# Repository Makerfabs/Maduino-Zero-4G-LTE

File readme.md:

# Maduino Zero 4G LTE

```c++
/*
Version:		V1.1
Author:			Vincent
Create Date:	2021/11/5
Note:
	2022/12/30	V1.1:	Change Wiki link.
*/
```

[toc]

# Makerfabs

[Makerfabs home page](https://www.makerfabs.com/)

[Makerfabs Wiki](https://wiki.makerfabs.com/)

# Maduino Zero 4G LTE
## Intruduce

Product Link ：[Maduino Zero 4G LTE(SIM7600X)](https://www.makerfabs.com/maduino-zero-4g-lte-sim7600.html) 

Wiki Link : [Maduino Zero 4G LTE](http://wiki.makerfabs.com/Maduino_Zero_4G_LTE.html) 

Maduino Zero 4G LTE integrated two types of the 4G LTE CAT4 module SIM7600A-H or SIM7600E-H, SIM7600A-H/SIM7600E-H is a complete multi-band LTE-FDD/LTE-TDD/HSPA+/UMTS/EDGE/GPRS/GSM module solution in LCC type which supports LTE CAT4 up to 150Mbps for downlink and 50Mbps for uplink data transfer, much faster and popular than 2G/3G.

## Module Type

## Feature

- Supports dial-up, phone, SMS, TCP, UDP, DTMF, HTTP, FTP, and so on
- Dual USB Type C port
- Control Via AT Commands
- Board USB supply voltage range: 4.8~5.5V, 5.0V Typical
- Board Battery supply voltage range: 3.4~4.2V, 3.7V Typical
- 3GPP E-UTRA Release 11
- Onboard charger, up to 1A charge current
- Overcharge protection(OCP), 4.3V
- Over-discharge protection(ODP), 2.5V
- Power Manager, the board can be supplied by USB or battery.
- IPEX Antenna, GSM/UMTS/LTE main antenna. UMTS/LTE auxiliary antenna. GNSS antenna
- SMS support
- Audio support
- On boarder controller: ATSAMD21G18A
- Audio chip: NAU8810
- Level Shifter: TXS0108E

### Front:

### Back:

### Frequency bands

### Transfer Speed

# Usage （Arduino）

## Equipment list

- Maduino Zero 4G (With GPS antenna and two 4G-GSM antennas)
- SIM card 

*Ensure that SIM7600 requirements are met and that the system can communicate with local carriers. We used China Mobile's 4G card for testing.*

## Compiler Options

**If you have any questions，such as how to install the development board, how to download the code, how to install the library. Please refer to :[Makerfabs_FAQ](https://github.com/Makerfabs/Makerfabs_FAQ)**

- Connect all antennas
- Insert a SIM card
- Connect **USB for MCU** to PC

- Upload codes, select "Arduino Zero" and "Native USB"

## Example List

### AT_command_demo

Input AT commands via serial monitor to learn how to use 4G module. This version is modify for SIM7600.

If define MODE_1A, when "1A" or "1A" is entered, 0x1A is sent to the module.

When sending SNS information, you need to send 0x1A to end the input.

### 4G_HTTP_DHT11_V1.0

Air temperature and humidity information detected by the DHT11 module is sent to ThingSpeak using a cellular network.

## AT Command Explain

###  AT commands test

Refer to the official AT manual of SIM7600 for detailed return values.

```c++
    AT+CGMI    // Request manufacturer identification
    AT+CGMM    // Request model identification
    AT+CGSN    // Request product serial number identification
    AT+CSUB    // Request the module version and chip
    AT+CPIN?     // Request the state of the SIM card
    AT+CICCID    // Read ICCID from SIM card
    AT+CNUM      // Request the subscriber number
    AT+CNMP?     // Preferred mode selection
    AT+COPS?     // Check the current network operator
```

### Get the GNSS location

GPS signal acquisition speed depends on signal strength, please wait patiently in an open place.

```c++
    AT+CGPS=1      // Start GPS session 
    AT+CGPSINFO    // Get GPS fixed position information
    AT+CGPS=0      // Stop GPS session
```

### Send and receive SMS

Please consult the operator for the phone number of the SMS center. The number "+8613800755500" in Shenzhen was used in the test. 

```c++
    AT+CSCA="XXXXXX"       // Set the SMS service centre address
    AT+CMGF=1              // Select SMS message format
    AT+CMGS="xxxxxx"       // Send message to "xxxxxx"(the receiver number).
```

"AT+CMGS" sets the phone number of the receiver and returns ' >' . Send desired content, such as "Send Massage Test!".After editing a short message, send it in hexadecimal format 1A Send a message.

*The Arduino IDE cannot send hexadecimal,  you can use other software. In the example code, entering 1A or 1A will send 0x1A to the module.*

# Usage （Raspberry Pi）

## Equipment list

- Maduino Zero 4G (With GPS antenna and two 4G-GSM antennas)
- SIM card 

*Ensure that SIM7600 requirements are met and that the system can communicate with local carriers. We used China Mobile's 4G card for testing.*

- Connect all antennas
- Insert a SIM card
- Connect **USB for MCU** to Raspberry Pi USB

## Used as a 4G network adapter

### Hardware Check

- Log in to the root account and perform all subsequent operations as the root account.

```shell
sudo su
```

- Install the Minicom serial port tool.

```shell
apt-get install minicom
```

- To view the serial port device, AT command serial port: "/dev/ttyUSB2"

```shell
ls /dev/ttyUSB*
```

- Open the serial port with Minicom

```shell
minicom -D /dev/ttyUSB2
```

- Enter the AT command in minicom

```shell
# Forcibly set the Internet access to 4G
AT+CNMP=38
# Querying network Quality
AT+CSQ
# Query the network registry
AT+CREG?
# Querying Network Carrier Information
AT+COPS?
# Querying network band
AT+CPSI?
```

- \- Press Ctrl + A, then X to exit Minicom

At this point, the hardware and network connections between SIM7600CE and Raspberry Pi are normal. This case uses the 4G card of China Mobile. If you cannot use the other areas, please ask SIMCOM. 

### Driver Install

By default, Raspbian is installed with Qualcomm driver files for the wwan0 network port. For Raspberry Pi, you need to uninstall the driver first (otherwise it will conflict with the new driver), and then install the Simcom's driver for wwan0.

- Check system drivers

```shell
lsmod
```

- Uninstalling an existing driver

```shell
rmmod qmi_wwan
```

- Install the raspberry PI kernel header file
```shell
apt install raspberrypi-kernel-headers
```
- Download the official driver program provided by SIMCOM
```shell
wget https://www.waveshare.net/w/upload/0/00/SIM7600_NDIS.7z
```
- Install the decompression tool and decompress it
```shell
apt-get install p7zip-full
7z x SIM7600_NDIS.7z -r -o ./SIM7600_NDIS
```
- Go to the driver folder and compile

```shell
cd SIM7600_NDIS
make clean
make
ls
```

- Install the driver module file

```shell
insmod simcom_wwan.ko
```

- Check whether the installation is successful
```shell
lsmod
```

### Assign IP addresses

- In this case, the wwan0 network port is displayed

```shell
ifconfig -a
```
- However, no IP address is assigned to the network port. To assign an IP address, enable the network port first

```shell
ifconfig wwan0 up
```
- Then, through Minicom, enter the AT command to start dialing

```shell
minicom -D /dev/ttyUSB2
AT$QCRMCALL=1,1
```
- Finally, exit Minicom and assign IP

```shell
apt-get install udhcpc
udhcpc -i wwan0
```
- Run the Ping command to check whether the network adapter is connected

```shell
ping -I wwan0 www.baidu.com
```

# Usage （Windows）

- Connect one end of USB cable to USB interface of PC and the other end to USB_LTE interface of Maduino Zero 4G LTE.

- Open the device manager and you can see these COM ports.

- If the COM port is identified in the figure above, but an exclamation mark appears, it indicates that the driver is not installed.
- Driver is in "Maduino-Zero-4G-LTE\win_driver\SIM7600X-Driver.7z"
- Open Device Manager - > Other equipment - >“SimTech,Incorporated”- >  Update the driver - > Browse my computer to find driver files - > Select a path for saving the driver file based on the system- >The installation is complete.

- Install the driver for each exclamation point
- The network icon will then appear as a cellular network.

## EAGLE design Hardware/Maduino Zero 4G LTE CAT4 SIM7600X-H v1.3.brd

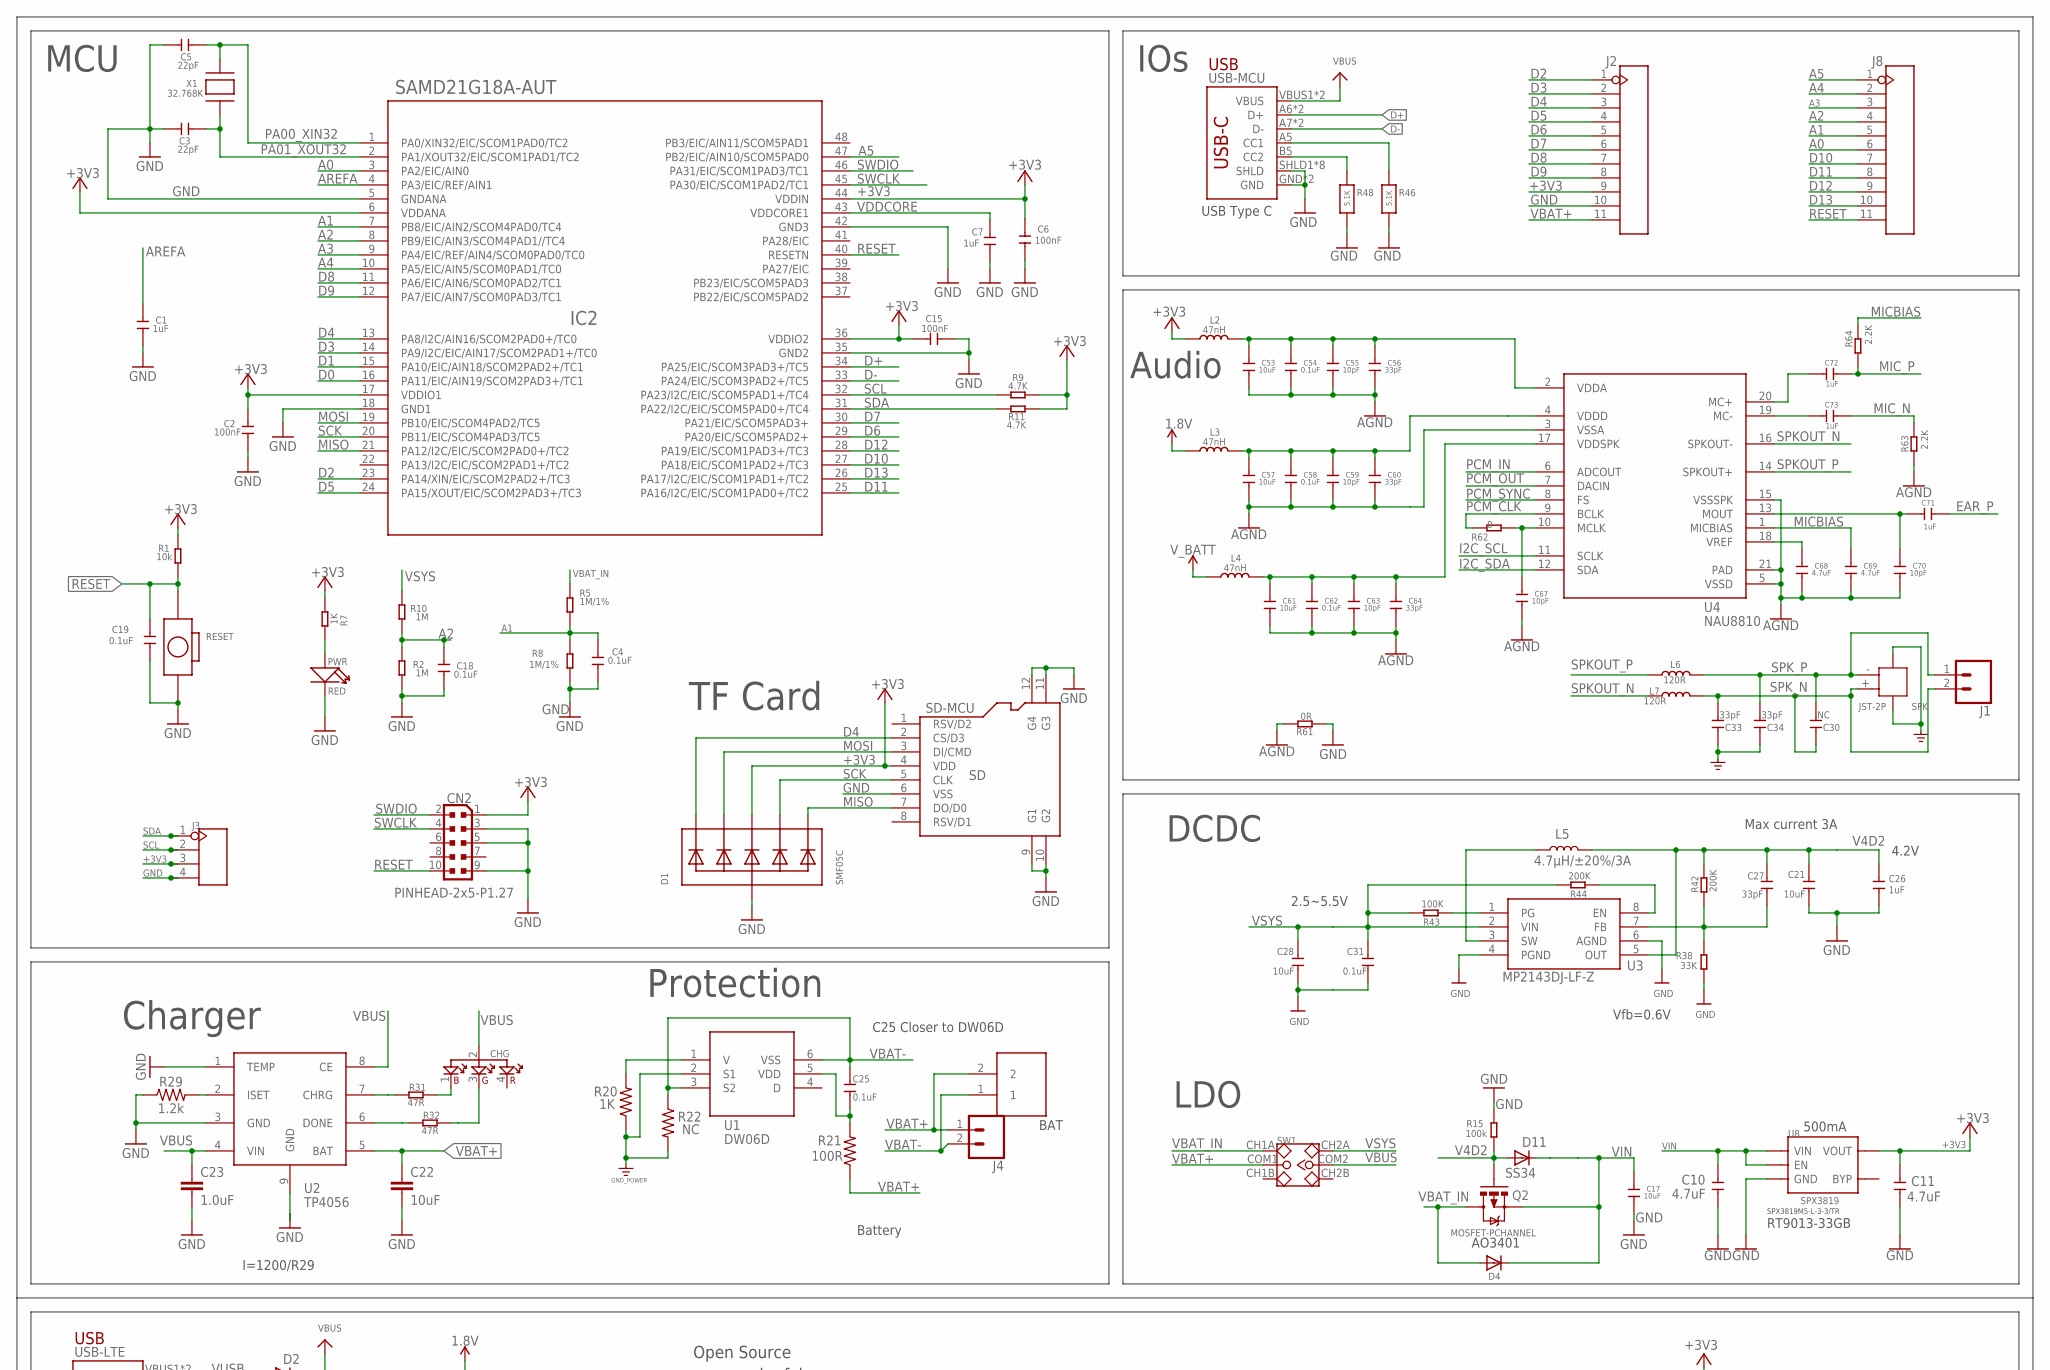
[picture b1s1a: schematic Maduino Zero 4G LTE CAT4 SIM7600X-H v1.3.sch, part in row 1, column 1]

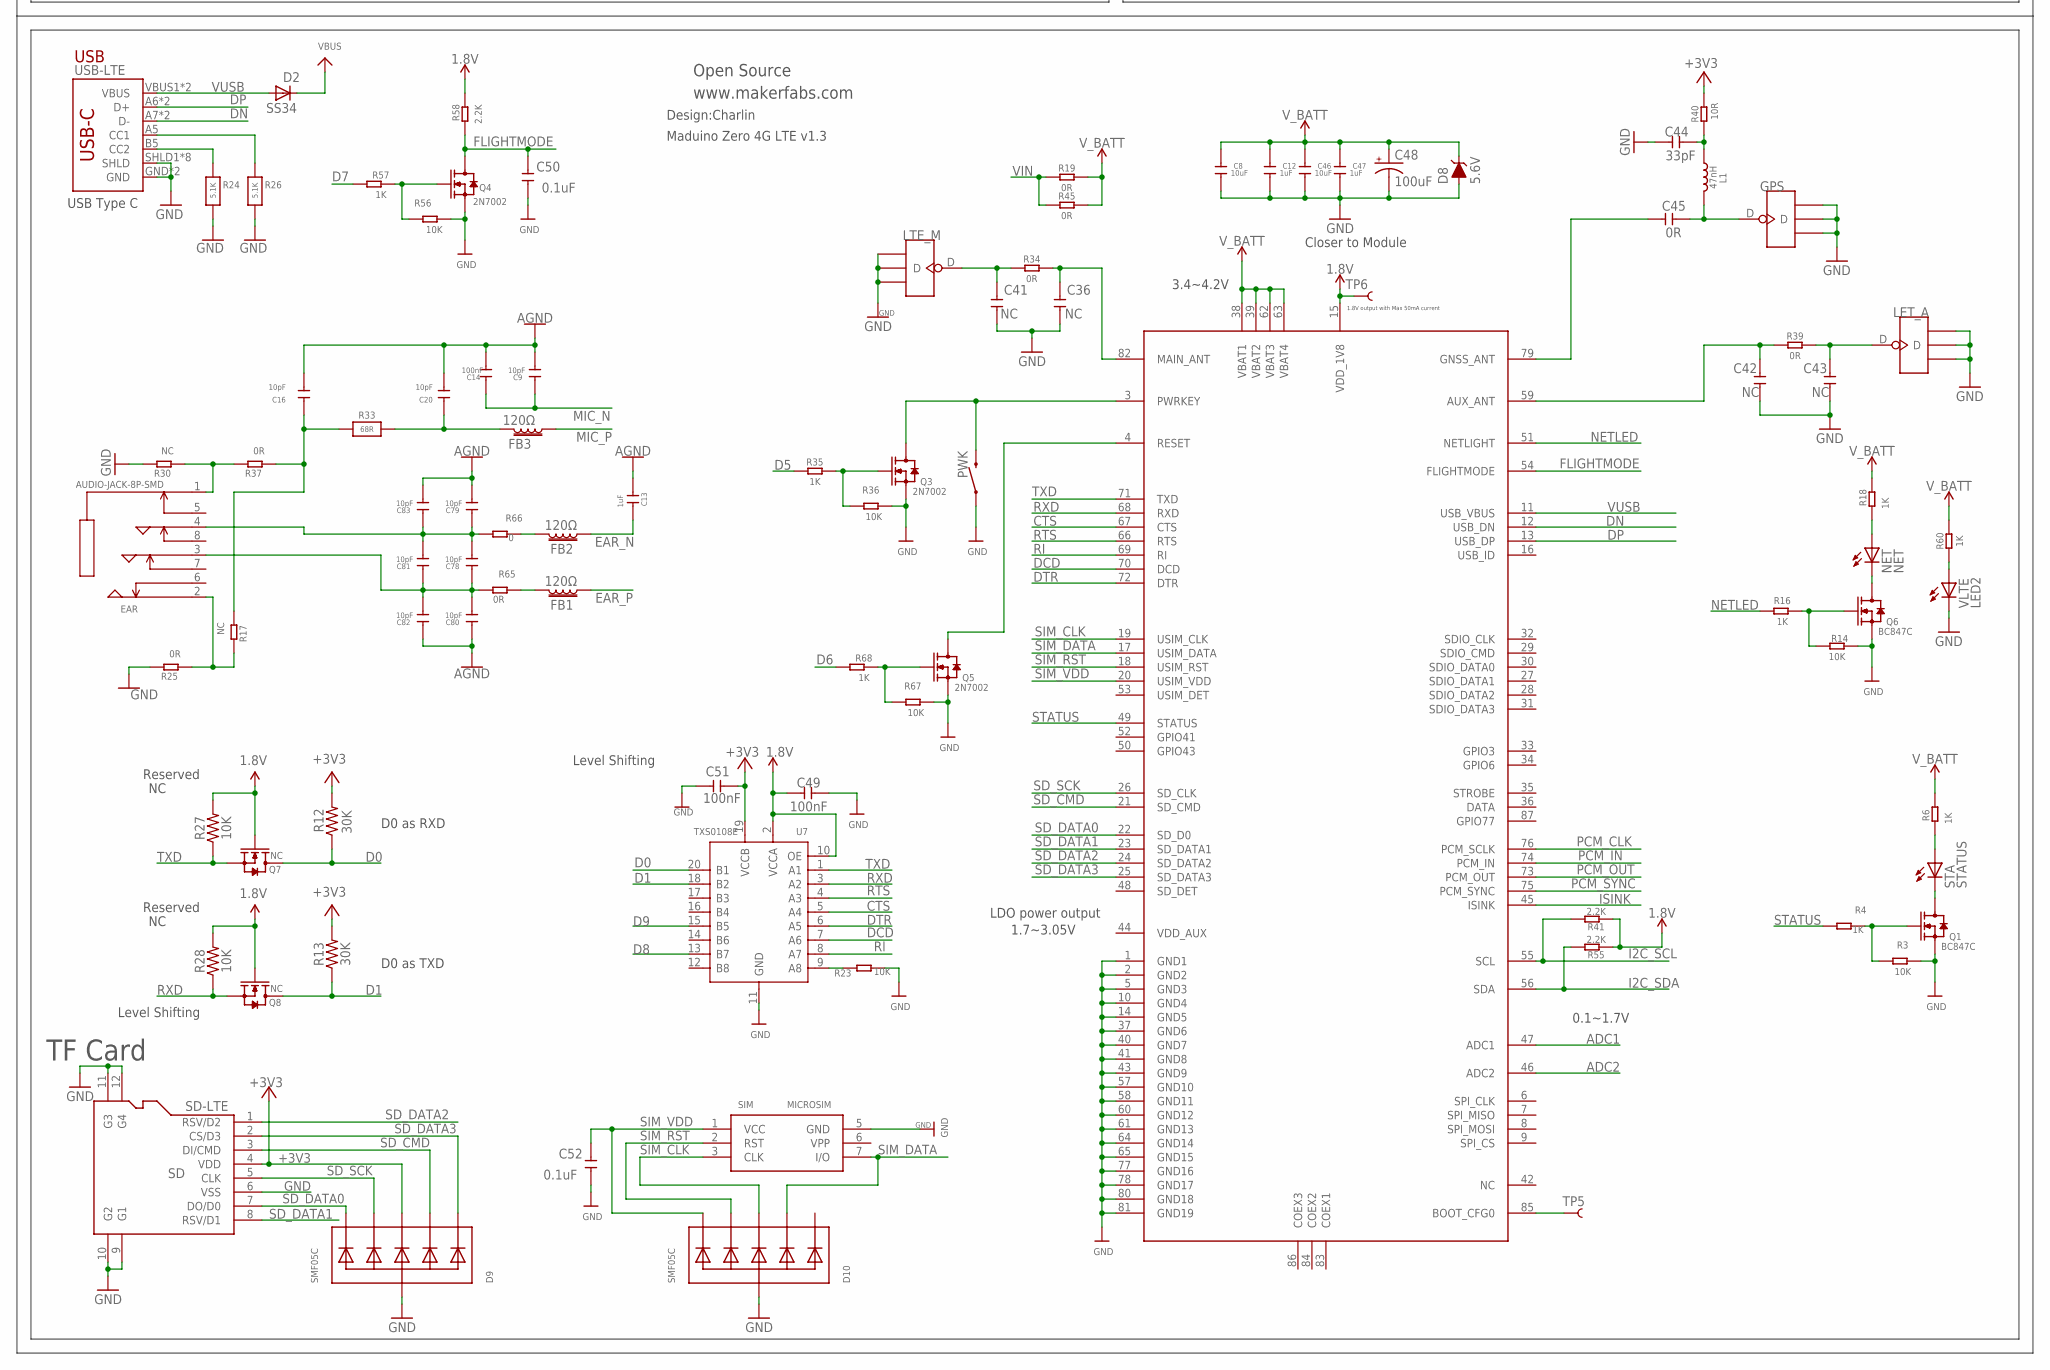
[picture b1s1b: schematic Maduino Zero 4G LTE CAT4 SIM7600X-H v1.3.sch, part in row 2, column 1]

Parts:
BAT: PH2.0-2P-90-DIP
C1, C7, C12, C13, C26, C47, C71, C72, C73: 1uF; 0603
C2, C6, C14, C15, C49, C51: 100nF; 0603
C3, C5: 22pF; 0603
C4, C18, C19, C25, C31, C50, C52, C54, C58, C62: 0.1uF; 0603
C8, C17, C21, C22, C28, C46, C53, C57, C61: 10uF; 0603
C9, C16, C20, C55, C59, C63, C67, C70, C78, C79, C80, C81, C82, C83: 10pF; 0603
C10, C11, C68, C69: 4.7uF; 0603
C23: 1.0uF; 0603
C27, C44, C56, C60, C64: 33pF; 0603
C30: NC; C0603
C33, C34: 33pF; C0603
C36, C41, C42, C43: NC; 0603
C45: 0R; 0603
C48: 100uF; EIA3528
CHG: E6C0606RGBC3UDA; SMD4-160L160W
CN2: PINHEAD-2x5-P1.27; PINHEAD_2X05_127
D1, D9, D10: SMF05C; SOT363
D2, D11: SS34; DO-214AC
D4: DIODESOD-323F; SOD-323F
D8: 5.6V; SOD-323
EAR: AUDIO-JACK-8P-SMD; AUDIO8P-SMD-3.5-14.5X6.1X4.0MM
FB1, FB2, FB3: 120Ω; 0603
GPS: ANTENNA-U-FL; 4P-U-FL
IC2: SAMD21G18A-AUT; TQFP48-7X7
J1, J4: CONN_02LOCK; 1X02_LOCK
J2, J8: HEADER-11P-2.54; 11P-2.54
J3: HEADER-4P-60/35MILROUND; 4P-65/35ROUND
L1, L2, L3, L4: 47nH; L0603
L5: 4.7µH/±20%/3A; SRN6045
L6, L7: 120R; L0603
LET_A: ANTENNA-U-FL; 4P-U-FL
LTE_M: ANTENNA-U-FL; 4P-U-FL
NET: NET; CHIP-LED0805
PWK: MOMENTARY-SWITCH-SPST-SMD-6.0X3.5MM; TACTILE_SWITCH_SMD_6.0X3.5MM
PWR: RED; LED-0603
Q1, Q6: BC847C; SOT23
Q2: MOSFET-PCHANNEL; SOT23-3
Q3, Q4, Q5: 2N7002; SOT23
Q7, Q8: NC; SOT23
R1: 10k; R0603
R2, R10: 1M; R0603
R3, R14, R23, R36, R56, R67: 10K; R0603
R4, R6, R7, R16, R18, R35, R57, R60, R68: 1K; R0603
R5, R8: 1M/1%; R0603
R9, R11: 4.7K; R0603
R12, R13: 30K; 0603
R15: 100k; R0603
R17, R30: NC; R0603
R19, R25, R34, R37, R39, R45, R61, R65: 0R; R0603
R20: 1K; 0603
R21: 100R; 0603
R22: NC; 0603
R24, R26, R46, R48: 5.1K; 0603-NO
R27, R28: 10K; 0603
R29: 1.2k; 0603
R31, R32: 47R; R0603
R33: 68R; 0603-NO
R38: 33K; R0603
R40: 10R; R0603
R41, R55, R58, R63, R64: 2.2K; R0603
R42, R44: 200K; R0603
R43: 100K; R0603
R62, R66: 0; R0603
RESET: BOTTON-2P-90D; 2P-7.62X3.56-90D
SD-LTE: SD; 8P-SMD
SD-MCU: SD; 8P-SMD
SIM: MICROSIM
SPK: JST-2P; HW2-SMD-2.0-90D
STA: STATUS; CHIP-LED0805
SW1: SWITCH-2CH-6P; 6P-2CH-2.54-7.6X3.0
TP5, TP6: TEST-POINT3; PAD.03X.03
U1: DW06D; SOT-23-6
U2: TP4056; SOP8-1.27P
U3: MP2143DJ-LF-Z; TSOT23-8
U4: NAU8810; QFN21-50P-400L400W
U6: SIM7600; SMD87-100P-3000L300W
U7: TXS0108E; TSSOP20-0.65-6.5X4.4MM
U8: SPX3819; SOT23-5
USB-LTE: USB_C5; USB-C-16P-5
USB-MCU: USB_C5; USB-C-16P-5
VLTE: LED2; CHIP-LED0805
X1: 32.768K; XTAL3215

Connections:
1.8V: C49.2, L3.1, Q7.1 (G), Q8.1 (G), R27.2, R28.2, R41.1, R55.1, R58.2, TP6.P$1, U6.15 (VDD_1V8), U7.2 (VCCA), U7.10 (OE)
+3V3: C2.2, C6.1, C11.2, C15.1, C51.1, CN2.1, D1.4 (C3), D9.4 (C3), IC2.6 (VDDANA), IC2.17 (VDDIO1), IC2.36 (VDDIO2), IC2.44 (VDDIN), J2.9, J3.3, L2.1, R1.2, R7.1, R9.2, R11.2, R12.2, R13.2, R40.2, SD-LTE.4 (VDD), SD-MCU.4 (VDD), U7.19 (VCCB), U8.5 (VOUT)
A0: IC2.3 (PA2/EIC/AIN0), J8.6
A1: C4.1, IC2.7 (PB8/EIC/AIN2/SCOM4PAD0/TC4), J8.5, R5.1, R8.2
A2: C18.1, IC2.8 (PB9/EIC/AIN3/SCOM4PAD1//TC4), J8.4, R2.2, R10.1
A3: IC2.9 (PA4/EIC/REF/AIN4/SCOM0PAD0/TC0), J8.3
A4: IC2.10 (PA5/EIC/AIN5/SCOM0PAD1/TC0), J8.2
A5: IC2.47 (PB2/EIC/AIN10/SCOM5PAD0), J8.1
ADC1: U6.47 (ADC1)
ADC2: U6.46 (ADC2)
AGND: C9.1, C13.2, C14.1, C16.1, C20.1, C53.1, C54.1, C55.1, C56.1, C57.1, C58.1, C59.1, C60.1, C61.1, C62.1, C63.1, C64.1, C67.1, C68.1, C69.1, C70.1, C79.1, C80.2, C82.2, C83.1, R61.2, R63.1, U4.3 (VSSA), U4.5 (VSSD), U4.15 (VSSSPK), U4.21 (PAD)
AREFA: C1.1, IC2.4 (PA3/EIC/REF/AIN1)
CTS: U6.67 (CTS), U7.5 (A4)
D0: IC2.16 (PA11/EIC/AIN19/SCOM2PAD3+/TC1), Q7.3 (D), R12.1, U7.20 (B1)
D1: IC2.15 (PA10/EIC/AIN18/SCOM2PAD2+/TC1), Q8.3 (D), R13.1, U7.18 (B2)
D2: IC2.23 (PA14/XIN/EIC/SCOM2PAD2+/TC3), J2.1
D3: IC2.14 (PA9/I2C/EIC/AIN17/SCOM2PAD1+/TC0), J2.2
D4: D1.1 (C1), IC2.13 (PA8/I2C/AIN16/SCOM2PAD0+/TC0), J2.3, SD-MCU.2 (CS/D3)
D5: IC2.24 (PA15/XOUT/EIC/SCOM2PAD3+/TC3), J2.4, R35.2
D6: IC2.29 (PA20/EIC/SCOM5PAD2+), J2.5, R68.2
D7: IC2.30 (PA21/EIC/SCOM5PAD3+), J2.6, R57.2
D8: IC2.11 (PA6/EIC/AIN6/SCOM0PAD2/TC1), J2.7, U7.13 (B7)
D9: IC2.12 (PA7/EIC/AIN7/SCOM0PAD3/TC1), J2.8, U7.15 (B5)
D10: IC2.27 (PA18/EIC/SCOM1PAD2+/TC3), J8.7
D11: IC2.25 (PA16/I2C/EIC/SCOM1PAD0+/TC2), J8.8
D12: IC2.28 (PA19/EIC/SCOM1PAD3+/TC3), J8.9
D13: IC2.26 (PA17/I2C/EIC/SCOM1PAD1+/TC2), J8.10
D+: IC2.34 (PA25/EIC/SCOM3PAD3+/TC5), USB-MCU.A6 (D+), USB-MCU.B6 (D+)
D-: IC2.33 (PA24/EIC/SCOM3PAD2+/TC5), USB-MCU.A7 (D-), USB-MCU.B7 (D-)
DCD: U6.70 (DCD), U7.7 (A6)
DN: U6.12 (USB_DN), USB-LTE.A7 (D-), USB-LTE.B7 (D-)
DONE: R32.2, U2.6 (DONE)
DP: U6.13 (USB_DP), USB-LTE.A6 (D+), USB-LTE.B6 (D+)
DTR: U6.72 (DTR), U7.6 (A5)
EAR_N: C13.1, FB2.1
EAR_P: C71.1, FB1.1
FLIGHTMODE: C50.2, Q4.3 (D), R58.1, U6.54 (FLIGHTMODE)
GND: C1.2, C2.1, C3.2, C4.2, C5.2, C6.2, C7.2, C8.1, C10.1, C11.1, C12.1, C15.2, C17.1, C18.2, C19.1, C21.1, C22.2, C23.2, C26.1, C28.1, C31.1, C33.2, C34.2, C36.1, C41.1, C42.1, C43.1, C44.2, C46.1, C47.1, C48.C (-), C49.1, C50.1, C51.2, C52.1, CN2.3, CN2.5, CN2.9, D1.2 (A), D8.A, D9.2 (A), D10.2 (A), GPS.GND1, GPS.GND2, GPS.GND3, IC2.5 (GNDANA), IC2.18 (GND1), IC2.35 (GND2), IC2.42 (GND3), J2.10, J3.4, LET_A.GND1, LET_A.GND2, LET_A.GND3, LTE_M.GND1, LTE_M.GND2, LTE_M.GND3, PWK.1, PWR.-, Q1.2 (S), Q3.2 (S), Q4.2 (S), Q5.2 (S), Q6.2 (S), R2.1, R3.1, R8.1, R14.1, R15.2, R20.1, R22.2, R23.1, R24.2, R25.2, R26.2, R29.1, R30.2, R36.1, R38.1, R46.2, R48.2, R56.1, R61.1, R67.1, RESET.P$2 (2), SD-LTE.6 (VSS), SD-LTE.9 (G1), SD-LTE.10 (G2), SD-LTE.11 (G3), SD-LTE.12 (G4), SD-MCU.6 (VSS), SD-MCU.9 (G1), SD-MCU.10 (G2), SD-MCU.11 (G3), SD-MCU.12 (G4), SIM.5 (GND), SPK.3, SPK.4, U1.2 (S1), U2.1 (TEMP), U2.3 (GND), U2.9 (GND), U3.4 (PGND), U3.6 (AGND), U6.1 (GND1), U6.2 (GND2), U6.5 (GND3), U6.10 (GND4), U6.14 (GND5), U6.37 (GND6), U6.40 (GND7), U6.41 (GND8), U6.43 (GND9), U6.57 (GND10), U6.58 (GND11), U6.60 (GND12), U6.61 (GND13), U6.64 (GND14), U6.65 (GND15), U6.77 (GND16), U6.78 (GND17), U6.80 (GND18), U6.81 (GND19), U7.11 (GND), U8.2 (GND), USB-LTE.GND, USB-LTE.GND2 (GND), USB-LTE.SHLD1 (SHLD), USB-LTE.SHLD2 (SHLD), USB-LTE.SHLD3 (SHLD), USB-LTE.SHLD4 (SHLD), USB-LTE.SHLD5 (SHLD), USB-LTE.SHLD6 (SHLD), USB-LTE.SHLD7 (SHLD), USB-LTE.SHLD8 (SHLD), USB-MCU.GND, USB-MCU.GND2 (GND), USB-MCU.SHLD1 (SHLD), USB-MCU.SHLD2 (SHLD), USB-MCU.SHLD3 (SHLD), USB-MCU.SHLD4 (SHLD), USB-MCU.SHLD5 (SHLD), USB-MCU.SHLD6 (SHLD), USB-MCU.SHLD7 (SHLD), USB-MCU.SHLD8 (SHLD), VLTE.C
I2C_SCL: R41.2, U4.11 (SCLK), U6.55 (SCL)
I2C_SDA: R55.2, U4.12 (SDA), U6.56 (SDA)
ISET: R29.2, U2.2 (ISET)
ISINK: U6.45 (ISINK)
MICBIAS: C69.2, R64.2, U4.1 (MICBIAS)
MIC_N: C9.2, C14.2, C73.1, R63.2
MIC_P: C72.1, FB3.1, R64.1
MISO: D1.6 (C5), IC2.21 (PA12/I2C/EIC/SCOM2PAD0+/TC2), SD-MCU.7 (DO/D0)
MOSI: D1.3 (C2), IC2.19 (PB10/EIC/SCOM4PAD2/TC5), SD-MCU.3 (DI/CMD)
unnamed: Q1.1 (G), R3.2, R4.1
unnamed: R6.1, STA.A
unnamed: PWR.+, R7.2
unnamed: Q1.3 (D), STA.C
unnamed: Q6.1 (G), R14.2, R16.1
unnamed: NET.A, R18.1
unnamed: NET.C, Q6.3 (D)
unnamed: TP5.P$1, U6.85 (BOOT_CFG0)
unnamed: C25.2, R21.2, U1.5 (VDD)
unnamed: R20.2, U1.1 (V)
unnamed: CHG.3, R32.1
unnamed: R31.2, U2.7 (CHRG)
unnamed: CHG.1, R31.1
unnamed: C16.2, R17.1, R33.1, R37.1
unnamed: C20.2, FB3.2, R33.2
unnamed: EAR.2, R17.2, R25.1
unnamed: R26.1, USB-LTE.A5 (CC1)
unnamed: R24.1, USB-LTE.B5 (CC2)
unnamed: EAR.1, R30.1, R37.2
unnamed: C78.1, C79.2, C81.1, C83.2, EAR.4, R66.1
unnamed: L5.1, U3.3 (SW)
unnamed: C27.1, R38.2, R42.1, U3.7 (FB)
unnamed: R23.2, U7.9 (A8)
unnamed: R46.1, USB-MCU.A5 (CC1)
unnamed: R48.1, USB-MCU.B5 (CC2)
unnamed: R43.1, U3.1 (PG)
unnamed: R44.1, U3.8 (EN)
unnamed: C36.2, R34.1, U6.82 (MAIN_ANT)
unnamed: C41.2, LTE_M.D, R34.2
unnamed: PWK.2, Q3.3 (D), U6.3 (PWRKEY)
unnamed: Q3.1 (G), R35.1, R36.2
unnamed: R60.1, VLTE.A
unnamed: C53.2, C54.2, C55.2, C56.2, L2.2, U4.2 (VDDA)
unnamed: C70.2, C71.2, U4.13 (MOUT)
unnamed: C61.2, C62.2, C63.2, C64.2, L4.2, U4.17 (VDDSPK)
unnamed: C68.2, U4.18 (VREF)
unnamed: C57.2, C58.2, C59.2, C60.2, L3.2, U4.4 (VDDD)
unnamed: C73.2, U4.19 (MC-)
unnamed: C67.2, R62.1, U4.10 (MCLK)
unnamed: C72.2, U4.20 (MC+)
unnamed: FB1.2, R65.2
unnamed: FB2.2, R66.2
unnamed: C78.2, C80.1, C81.2, C82.1, EAR.3, R65.1
unnamed: Q5.3 (D), U6.4 (RESET)
unnamed: Q5.1 (G), R67.2, R68.1
unnamed: C43.2, LET_A.D, R39.2
unnamed: C44.1, L1.1, R40.1
unnamed: C42.2, R39.1, U6.59 (AUX_ANT)
unnamed: C45.2, U6.79 (GNSS_ANT)
unnamed: C45.1, GPS.D, L1.2
unnamed: Q4.1 (G), R56.2, R57.1
NETLED: R16.2, U6.51 (NETLIGHT)
PA00_XIN32: C5.1, IC2.1 (PA0/XIN32/EIC/SCOM1PAD0/TC2), X1.P$2
PA01_XOUT32: C3.1, IC2.2 (PA1/XOUT32/EIC/SCOM1PAD1/TC2), X1.P$1
PCM_CLK: R62.2, U4.9 (BCLK), U6.76 (PCM_SCLK)
PCM_IN: U4.6 (ADCOUT), U6.74 (PCM_IN)
PCM_OUT: U4.7 (DACIN), U6.73 (PCM_OUT)
PCM_SYNC: U4.8 (FS), U6.75 (PCM_SYNC)
RESET: C19.2, CN2.10, IC2.40 (RESETN), J8.11, R1.1, RESET.P$1 (1)
RI: U6.69 (RI), U7.8 (A7)
RTS: U6.66 (RTS), U7.4 (A3)
RXD: Q8.2 (S), R28.1, U6.68 (RXD), U7.3 (A2)
SCK: D1.5 (C4), IC2.20 (PB11/EIC/SCOM4PAD3/TC5), SD-MCU.5 (CLK)
SCL: IC2.32 (PA23/I2C/EIC/SCOM5PAD1+/TC4), J3.2, R9.1
SDA: IC2.31 (PA22/I2C/EIC/SCOM5PAD0+/TC4), J3.1, R11.1
SD_CMD: D9.3 (C2), SD-LTE.3 (DI/CMD), U6.21 (SD_CMD)
SD_DATA0: D9.6 (C5), SD-LTE.7 (DO/D0), U6.22 (SD_D0)
SD_DATA1: SD-LTE.8 (RSV/D1), U6.23 (SD_DATA1)
SD_DATA2: SD-LTE.1 (RSV/D2), U6.24 (SD_DATA2)
SD_DATA3: D9.1 (C1), SD-LTE.2 (CS/D3), U6.25 (SD_DATA3)
SD_SCK: D9.5 (C4), SD-LTE.5 (CLK), U6.26 (SD_CLK)
SIM_CLK: D10.4 (C3), SIM.3 (CLK), U6.19 (USIM_CLK)
SIM_DATA: D10.3 (C2), SIM.7 (I/O), U6.17 (USIM_DATA)
SIM_RST: D10.5 (C4), SIM.2 (RST), U6.18 (USIM_RST)
SIM_VDD: C52.2, D10.6 (C5), SIM.1 (VCC), U6.20 (USIM_VDD)
SPKOUT_N: L7.1, U4.16 (SPKOUT-)
SPKOUT_P: L6.1, U4.14 (SPKOUT+)
SPK_N: C30.2, C33.1, J1.2, L7.2, SPK.+ (1)
SPK_P: C30.1, C34.1, J1.1, L6.2, SPK.- (2)
STATUS: R4.2, U6.49 (STATUS)
SWCLK: CN2.4, IC2.45 (PA30/EIC/SCOM1PAD2/TC1)
SWDIO: CN2.2, IC2.46 (PA31/EIC/SCOM1PAD3/TC1)
TXD: Q7.2 (S), R27.1, U6.71 (TXD), U7.1 (A1)
V4D2: C21.2, C26.2, C27.2, D11.A, L5.2, Q2.1 (G), R15.1, R42.2, U3.5 (OUT)
VBAT+: BAT.2, C22.1, J2.11, J4.1, R21.1, SW1.COM1, U2.5 (BAT)
VBAT-: BAT.1, C25.1, J4.2, R22.1, U1.3 (S2), U1.6 (VSS)
VBAT_IN: D4.A, Q2.3 (D), R5.2, SW1.CH1A
VBUS: C23.1, CHG.2, D2.C, SW1.COM2, U2.4 (VIN), U2.8 (CE), USB-MCU.VBUS1 (VBUS), USB-MCU.VBUS2 (VBUS)
VDDCORE: C7.1, IC2.43 (VDDCORE1)
VIN: C10.2, C17.2, D4.C, D11.C, Q2.2 (S), R19.2, R45.2, U8.1 (VIN), U8.3 (EN)
VSYS: C28.2, C31.2, R10.2, R43.2, R44.2, SW1.CH2A, U3.2 (VIN)
VUSB: D2.A, U6.11 (USB_VBUS), USB-LTE.VBUS1 (VBUS), USB-LTE.VBUS2 (VBUS)
V_BATT: C8.2, C12.2, C46.2, C47.2, C48.A (+), D8.C, L4.1, R6.2, R18.2, R19.1, R45.1, R60.2, U6.38 (VBAT1), U6.39 (VBAT2), U6.62 (VBAT3), U6.63 (VBAT4)

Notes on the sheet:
500mA
www.makerfabs.com
MCU
IOs
LDO
Design:Charlin
Open Source
AO3401
Maduino Zero 4G LTE v1.3
Closer to Module
1.8V output with Max 50mA current
LDO power output
3.4~4.2V
0.1~1.7V
1.7~3.05V
Battery
C25 Closer to DW06D
Protection
BAT
I=1200/R29
Level Shifting
Reserved
USB
USB Type C
TF Card
Audio
Charger
D0 as RXD
D0 as TXD
SPX3819M5-L-3-3/TR
RT9013-33GB
4.2V
Max current 3A
Vfb=0.6V
2.5~5.5V
DCDC

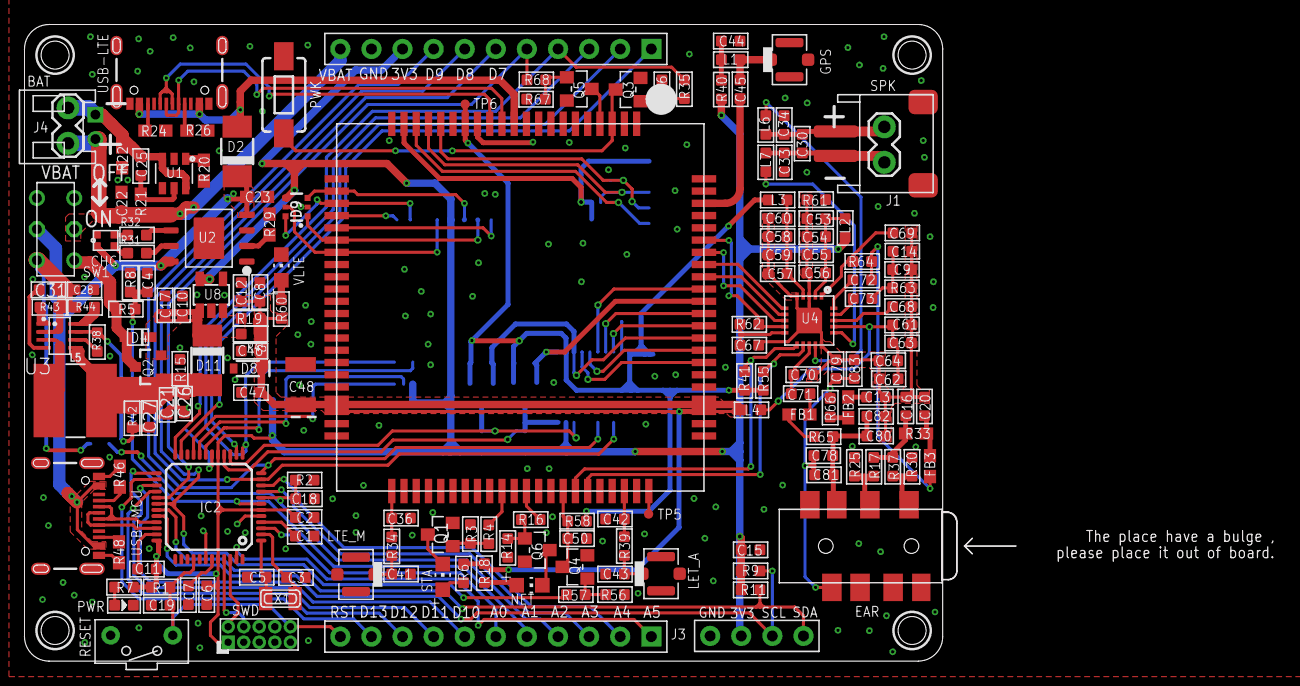
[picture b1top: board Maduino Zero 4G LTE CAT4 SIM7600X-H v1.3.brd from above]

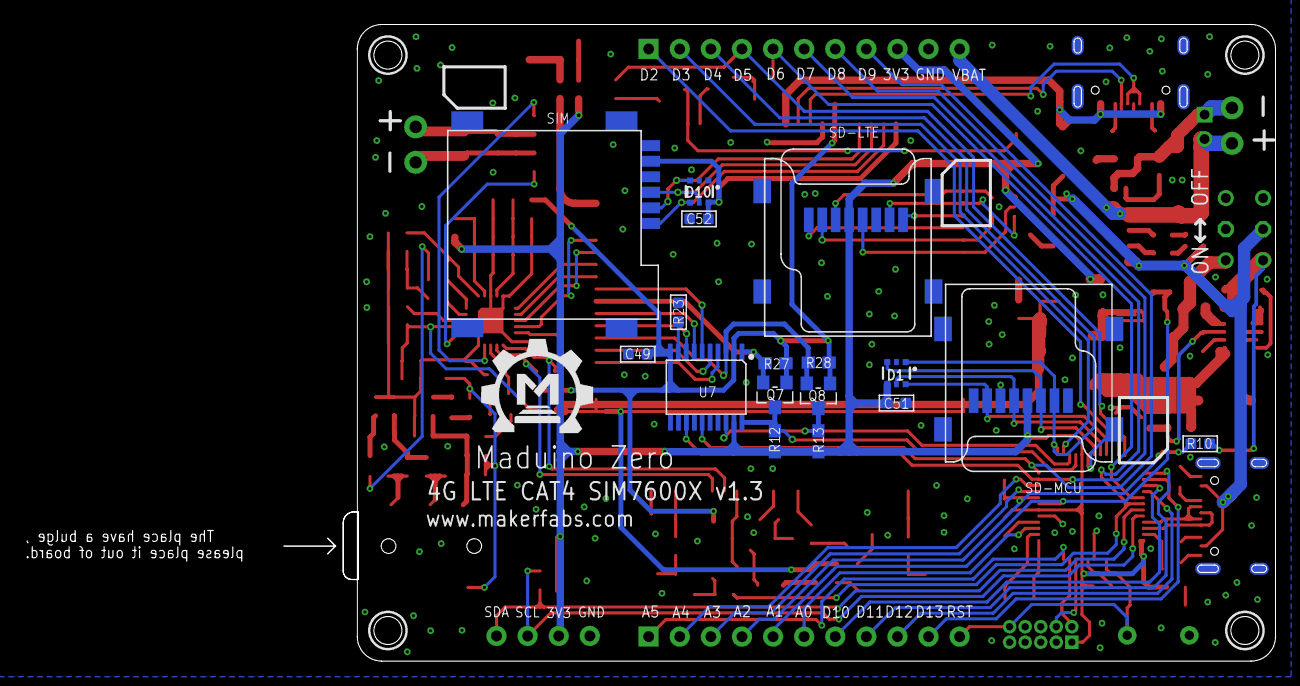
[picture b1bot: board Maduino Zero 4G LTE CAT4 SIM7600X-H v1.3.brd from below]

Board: 2 copper layers, 81.0 x 52.0 mm, 191 parts (18 on the bottom side), 137 nets.

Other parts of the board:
U$1: MAKERFABS_0.3

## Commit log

2021-11-04 Not Ready
2021-11-04 Create hardware and AT command
2021-11-04 Create SD_MCU_test
2021-11-05 Fix at command demo
2021-11-05 Edit readme
2021-11-05 Create http_DHT11
2021-11-08 Add files via upload
    new pic
2021-11-08 Add files via upload
    update pic
2021-11-08 Add files via upload
    add hardware
2021-11-09 add pic
2021-11-09 Add Win Driver
2026-04-20 Updates the hardware
2026-05-07 Update the file name

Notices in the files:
parts and their libraries:
microbuilder: This work is placed in the public domain, and may be freely used for commercial and non-commercial work with the following conditions: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
User-Submitted: Licensing: Creative Commons ShareAlike 4.0 International - https://creativecommons.org/licenses/by-sa/4.0
